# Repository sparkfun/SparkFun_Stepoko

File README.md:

SparkFun GRBL Board
========================================

[*SparkFun Stepoko (ROB-13155)*](https://www.sparkfun.com/products/13155)

A 3 axis motor controller for use with grbl.

Repository Contents (template)
-------------------

* **/Examples** - Example gcode files, projects, and settings
* **/Hardware** - Eagle design files (.brd, .sch)
* **/Mechanical** - Enclosure and heatsink mechanical drawings
* **/Production** - Production panel files (.brd)

Documentation
--------------
* **Hookup Guide** - Basic hookup guide for the Stepoko
* **Coaster Project Tutorial** - Process of creating the coaster example
* **[SparkFun Fritzing repo](https://github.com/sparkfun/Fritzing_Parts)** - Fritzing diagrams for SparkFun products.
* **[SparkFun 3D Model repo](https://github.com/sparkfun/3D_Models)** - 3D models of SparkFun products. 

Product Versions
----------------
[*SparkFun Stepoko (ROB-13155)*](https://www.sparkfun.com/products/13155)

Version History
---------------
* [v1.0](https://github.com/sparkfun/SparkFun_Stepoko/tree/V_1_0) - Released to Reds
* [v1.1](https://github.com/sparkfun/SparkFun_Stepoko/tree/V_1_1) - Changed pot symbol name and 'top-side' resistor value
* [v1.2](https://github.com/sparkfun/SparkFun_Stepoko/tree/V_1_2) - Updated capacitor values, documentation finished

License Information
-------------------

This product is _**open source**_! 

Please review the LICENSE.md file for license information. 

If you have any questions or concerns on licensing, please contact techsupport@sparkfun.com.

Distributed as-is; no warranty is given.

- Your friends at SparkFun.

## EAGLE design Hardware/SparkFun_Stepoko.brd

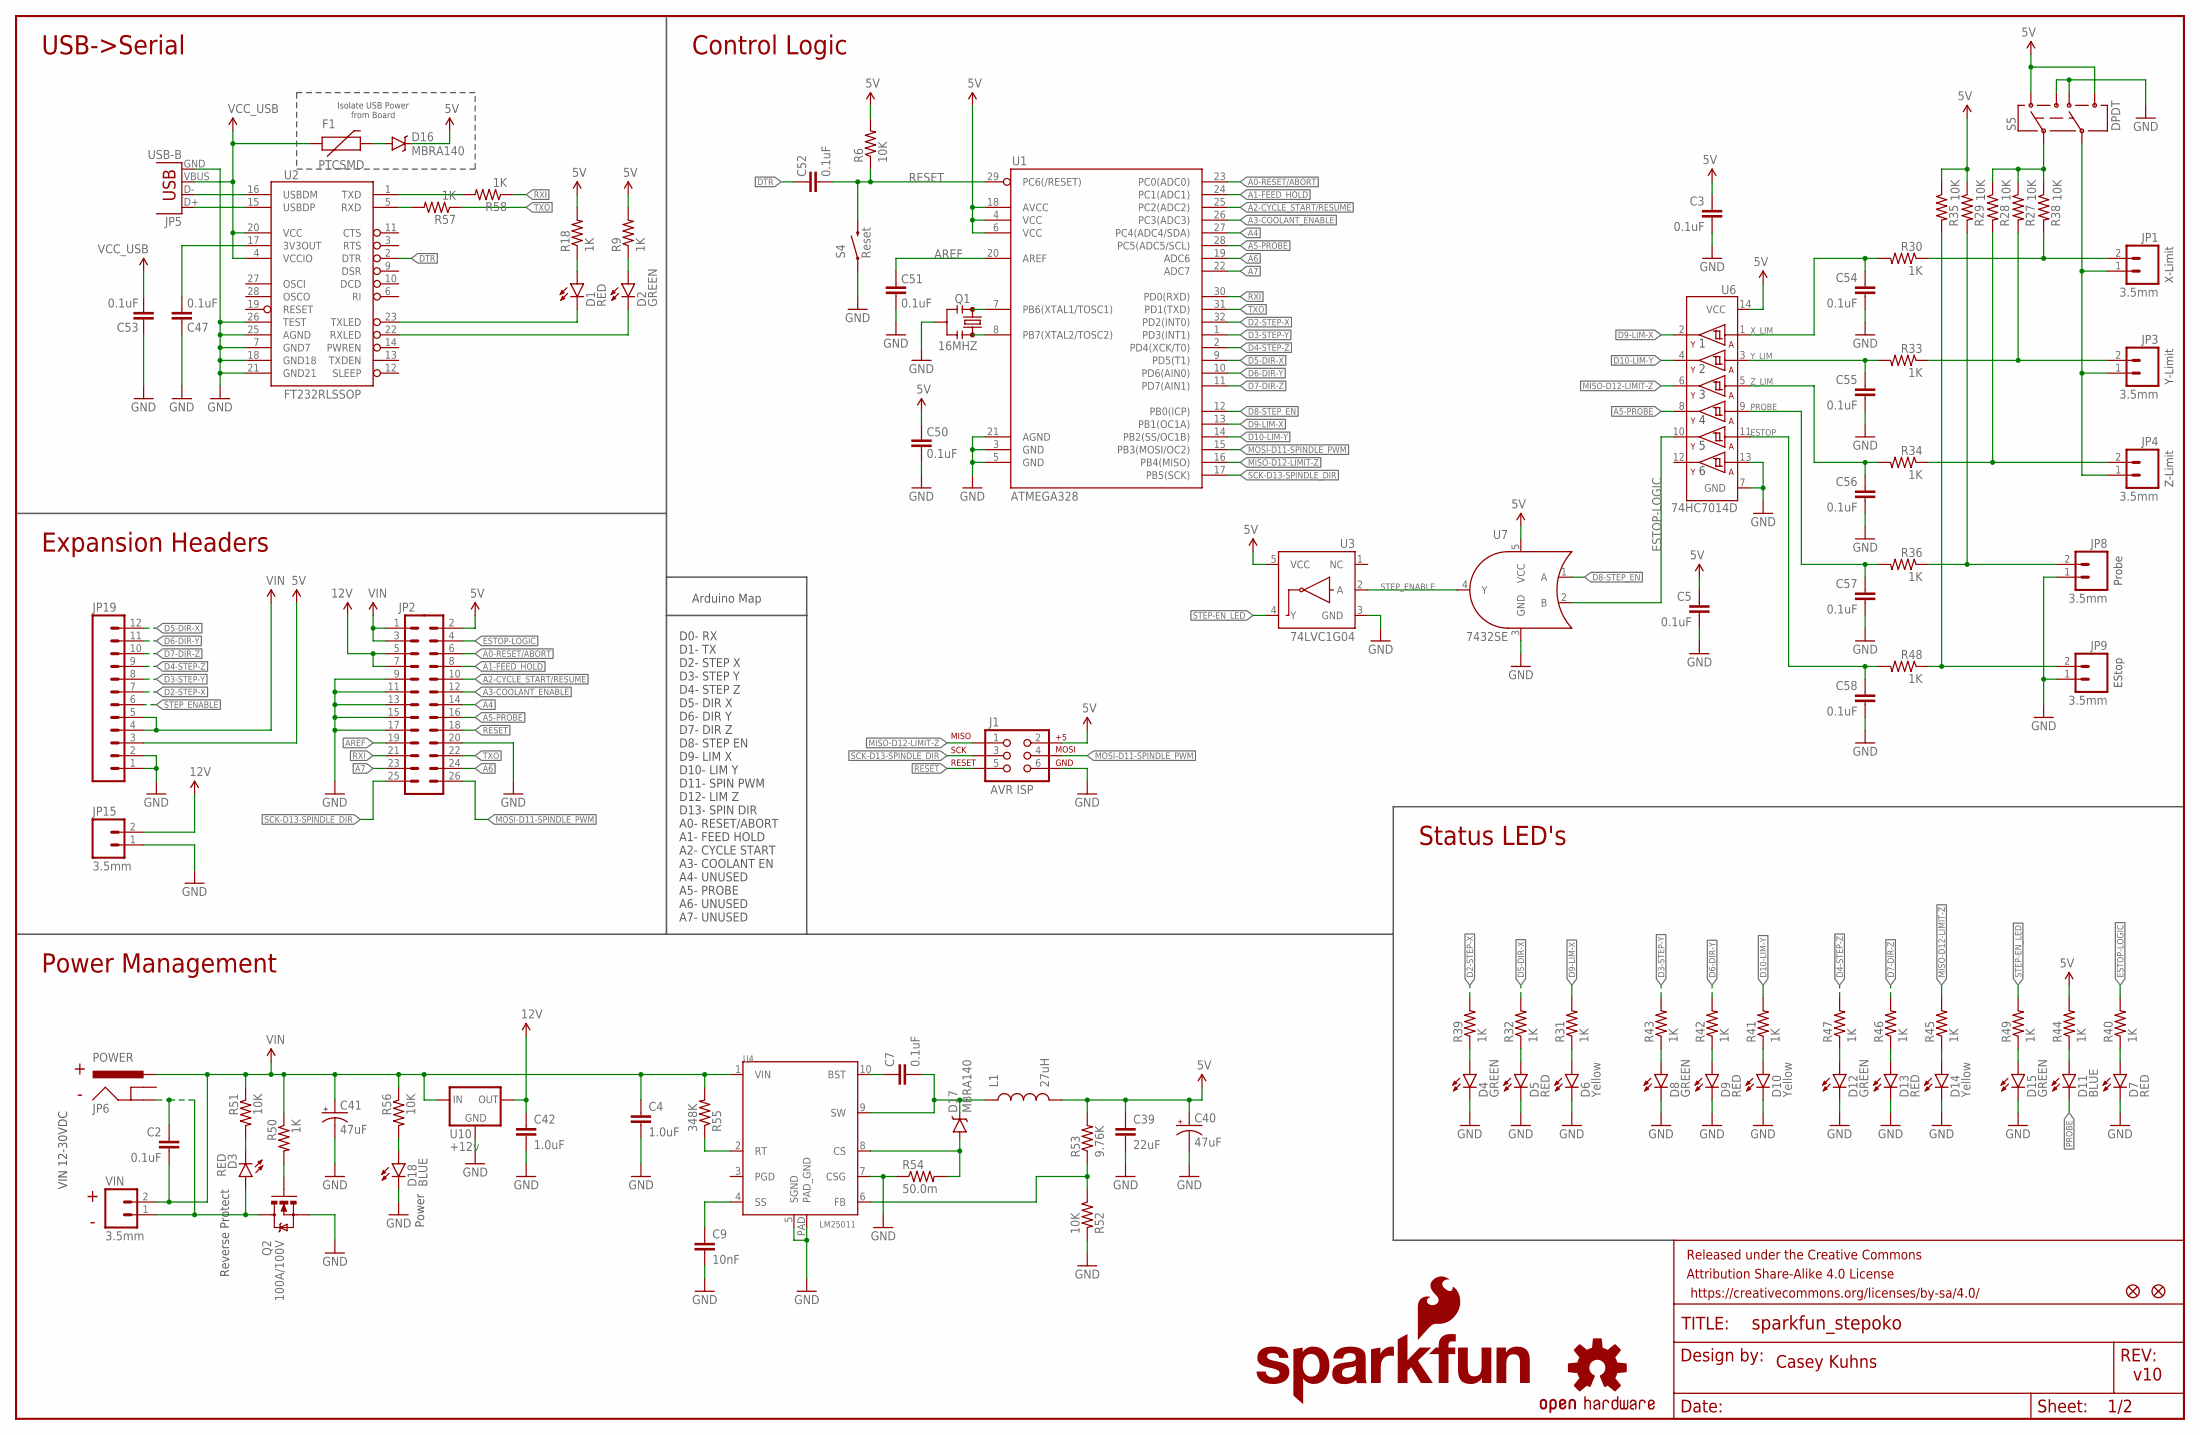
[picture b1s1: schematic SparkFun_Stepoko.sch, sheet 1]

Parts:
C2, C3, C5, C7, C47, C50, C51, C52, C53, C54, C55, C56, C57, C58: 0.1uF; 0603-CAP
C4, C42: 1.0uF; 1206-CAP
C9: 10nF; 0603-CAP
C39: 22uF; 1210
C40, C41: 47uF; PANASONIC_D
D1, D3, D5, D7, D9, D13: RED; LED-1206
D2, D4, D8, D12, D15: GREEN; LED-1206
D6, D10, D14: Yellow; LED-1206
D11, D18: BLUE; LED-1206
D16, D17: MBRA140; SMA-DIODE
F1: PTCSMD; PTC-1206
FID1, FID2: FIDUCIAL1X2; FIDUCIAL-1X2
FRAME1: FRAME-LEDGER; CREATIVE_COMMONS
J1: AVR ISP; 2X3
JP1, JP3, JP4, JP8, JP9, JP15: 3.5mm; SCREWTERMINAL-3.5MM-2_LOCK
JP2: M13X22X13; 2X13
JP5: USB-B; USB-B-PTH
JP6: POWER; POWER_JACK_PTH_LOCK
JP19: M12PTH; 1X12
L1: 27uH; INDUCTOR_SDR1307
LOGO1: OSHW-LOGOM; OSHW-LOGO-M
LOGO3: SFE_LOGO_NAME_FLAME.2_INCH; SFE_LOGO_NAME_FLAME_.2
Q1: 16MHZ; RESONATOR-SMD
Q2: 100A/100V; TO-263/D2PAK
R6, R27, R28, R29, R35, R38, R51, R52, R56: 10K; 0603-RES
R9, R18, R30, R33, R34, R36, R48, R50, R57, R58: 1K; 0603-RES@1
R31, R32, R39, R40, R41, R42, R43, R44, R45, R46, R47, R49: 1K; 0603-RES
R53: 9.76K; 0603
R54: 50.0m; 0603
R55: 348K; 0603
S4: Reset; TACTILE-SWITCH-SMD
S5: DPDT; AYZ0202
U1: ATMEGA328; TQFP32-08@1
U2: FT232RLSSOP; SSOP28DB
U3: 74LVC1G04; SOT353
U4: LM25011; HVSS0P-10
U6: 74HC7014D; SOIC-14
U7: 7432SE; SOT353
U10: +12v; TO-252
VIN: 3.5mm; SCREWTERMINAL-3.5MM-2_LOCK

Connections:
5V: C3.1, C5.1, C39.1, C40.+, C50.2, D16.C, J1.2, JP2.2, JP19.3, L1.P$2 (2), R6.2, R9.2, R18.2, R29.1, R35.1, R44.2, R53.2, S5.1, S5.6, U1.4 (VCC), U1.6 (VCC), U1.18 (AVCC), U3.5 (VCC), U6.14 (VCC), U7.5 (VCC); also elsewhere on the board
A0-RESET/ABORT: JP2.6, U1.23 (PC0(ADC0))
A1-FEED_HOLD: JP2.8, U1.24 (PC1(ADC1))
A2-CYCLE_START/RESUME: JP2.10, U1.25 (PC2(ADC2))
A3-COOLANT_ENABLE: JP2.12, U1.26 (PC3(ADC3))
A4: JP2.14, U1.27 (PC4(ADC4/SDA))
A5-PROBE: JP2.16, U1.28 (PC5(ADC5/SCL)), U6.8 (4Y)
A6: JP2.24, U1.19 (ADC6)
A7: JP2.23, U1.22 (ADC7)
AREF: C51.2, JP2.19, U1.20 (AREF)
D2-STEP-X: JP19.7, R39.2, U1.32 (PD2(INT0)); also elsewhere on the board
D3-STEP-Y: JP19.8, R43.2, U1.1 (PD3(INT1)); also elsewhere on the board
D4-STEP-Z: JP19.9, R47.2, U1.2 (PD4(XCK/T0)); also elsewhere on the board
D5-DIR-X: JP19.12, R32.2, U1.9 (PD5(T1)); also elsewhere on the board
D6-DIR-Y: JP19.11, R42.2, U1.10 (PD6(AIN0)); also elsewhere on the board
D7-DIR-Z: JP19.10, R46.2, U1.11 (PD7(AIN1)); also elsewhere on the board
D8-STEP_EN: U1.12 (PB0(ICP)), U7.1 (A)
D9-LIM-X: R31.2, U1.13 (PB1(OC1A)), U6.2 (1Y)
D10-LIM-Y: R41.2, U1.14 (PB2(SS/OC1B)), U6.4 (2Y)
D+: JP5.D+, U2.15 (USBDP)
D-: JP5.D-, U2.16 (USBDM)
DTR: C52.2, U2.2 (DTR)
ESTOP: C58.1, R48.2, U6.11 (5A)
ESTOP-LOGIC: JP2.4, R40.2, U6.10 (5Y), U7.2 (B)
GND: C3.2, C4.2, C5.2, C9.2, C39.2, C40.-, C41.-, C42.2, C47.2, C50.1, C51.1, C53.2, C54.2, C55.2, C56.2, C57.2, C58.2, D4.C, D5.C, D6.C, D7.C, D8.C, D9.C, D10.C, D12.C, D13.C, D14.C, D15.C, D18.C, J1.6, JP2.9, JP2.11, JP2.13, JP2.15, JP2.17, JP2.20, JP5.GND, JP8.1, JP9.1, JP15.1, JP19.1, JP19.2, Q1.2, Q2.3 (S), R52.2, R54.1, S4.1, S5.3, S5.4, U1.3 (GND), U1.5 (GND), U1.21 (AGND), U2.7 (GND7), U2.18 (GND18), U2.21 (GND21), U2.25 (AGND), U2.26 (TEST), U3.3 (GND), U4.5 (SGND), U4.7 (CSG), U4.PAD (PAD_GND), U6.7 (GND), U6.13 (6A), U7.3 (GND), U10.3 (GND); also elsewhere on the board
MISO-D12-LIMIT-Z: J1.1, R45.2, U1.16 (PB4(MISO)), U6.6 (3Y)
MOSI-D11-SPINDLE_PWM: J1.4, JP2.26, U1.15 (PB3(MOSI/OC2))
unnamed: R58.2, U2.1 (TXD)
unnamed: D2.A, R9.1
unnamed: D1.A, R18.1
unnamed: JP1.1, JP3.1, JP4.1, S5.5
unnamed: D7.A, R40.1
unnamed: Q1.3, U1.8 (PB7(XTAL2/TOSC2))
unnamed: JP1.2, R30.1, R38.2
unnamed: Q1.1, U1.7 (PB6(XTAL1/TOSC1))
unnamed: D11.A, R44.1
unnamed: D15.A, R49.1
unnamed: C2.1, D3.A, JP6.GND, Q2.2 (D), VIN.1
unnamed: D6.A, R31.1
unnamed: D5.A, R32.1
unnamed: D4.A, R39.1
unnamed: R52.1, R53.1, U4.6 (FB)
unnamed: D10.A, R41.1
unnamed: D9.A, R42.1
unnamed: D1.C, U2.23 (TXLED)
unnamed: D2.C, U2.22 (RXLED)
unnamed: D8.A, R43.1
unnamed: Q2.1 (G), R50.2
unnamed: D14.A, R45.1
unnamed: D3.C, R51.2
unnamed: JP3.2, R27.2, R33.1
unnamed: JP4.2, R28.2, R34.1
unnamed: D16.A, F1.2
unnamed: JP8.2, R29.2, R36.1
unnamed: JP9.2, R35.2, R48.1
unnamed: D18.A, R56.2
unnamed: D13.A, R46.1
unnamed: D12.A, R47.1
unnamed: R57.2, U2.5 (RXD)
unnamed: R55.1, U4.2 (RT)
unnamed: C7.1, U4.10 (BST)
unnamed: C7.2, D17.C, L1.P$1 (1), U4.9 (SW)
unnamed: C9.1, U4.4 (SS)
unnamed: R27.1, R28.1, R38.1, S5.2
unnamed: D17.A, R54.2, U4.8 (CS)
unnamed: C47.1, U2.17 (3V3OUT)
PROBE: C57.1, D11.C, R36.2, U6.9 (4A)
RESET: C52.1, J1.5, JP2.18, R6.1, S4.3 (2), U1.29 (PC6(/RESET))
RXI: JP2.21, R58.1, U1.30 (PD0(RXD))
SCK-D13-SPINDLE_DIR: J1.3, JP2.25, U1.17 (PB5(SCK))
STEP-EN_LED: R49.2, U3.4 (Y)
STEP_ENABLE: JP19.6, U3.2 (A), U7.4 (Y); also elsewhere on the board
TXO: JP2.22, R57.1, U1.31 (PD1(TXD))
VCC: C42.1, JP2.5, JP2.7, JP15.2, U10.2 (OUT)
VCC_USB: C53.1, F1.1, JP5.VBUS, U2.4 (VCCIO), U2.20 (VCC)
VIN: C2.2, C4.1, C41.+, JP2.1, JP2.3, JP6.PWR, JP19.4, JP19.5, R50.1, R51.1, R55.2, R56.1, U4.1 (VIN), U10.1 (IN), VIN.2; also elsewhere on the board
X_LIM: C54.1, R30.2, U6.1 (1A)
Y_LIM: C55.1, R33.2, U6.3 (2A)
Z_LIM: C56.1, R34.2, U6.5 (3A)

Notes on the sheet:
X-Limit
Y-Limit
Z-Limit
Probe
EStop
Isolate USB Power from Board
Status LED's
Power Management
Expansion Headers
USB->Serial
Control Logic
Reverse Protect
Power
Casey Kuhns
v10
D0- RX D1- TX D2- STEP X D3- STEP Y D4- STEP Z D5- DIR X D6- DIR Y D7- DIR Z D8- STEP EN D9- LIM X D10- LIM Y D11- SPIN PWM D12- LIM Z D13- SPIN DIR A0- RESET/ABORT A1- FEED HOLD A2- CYCLE START A3- COOLANT EN A4- UNUSED A5- PROBE A6- UNUSED A7- UNUSED
Arduino Map
VIN 12-30VDC

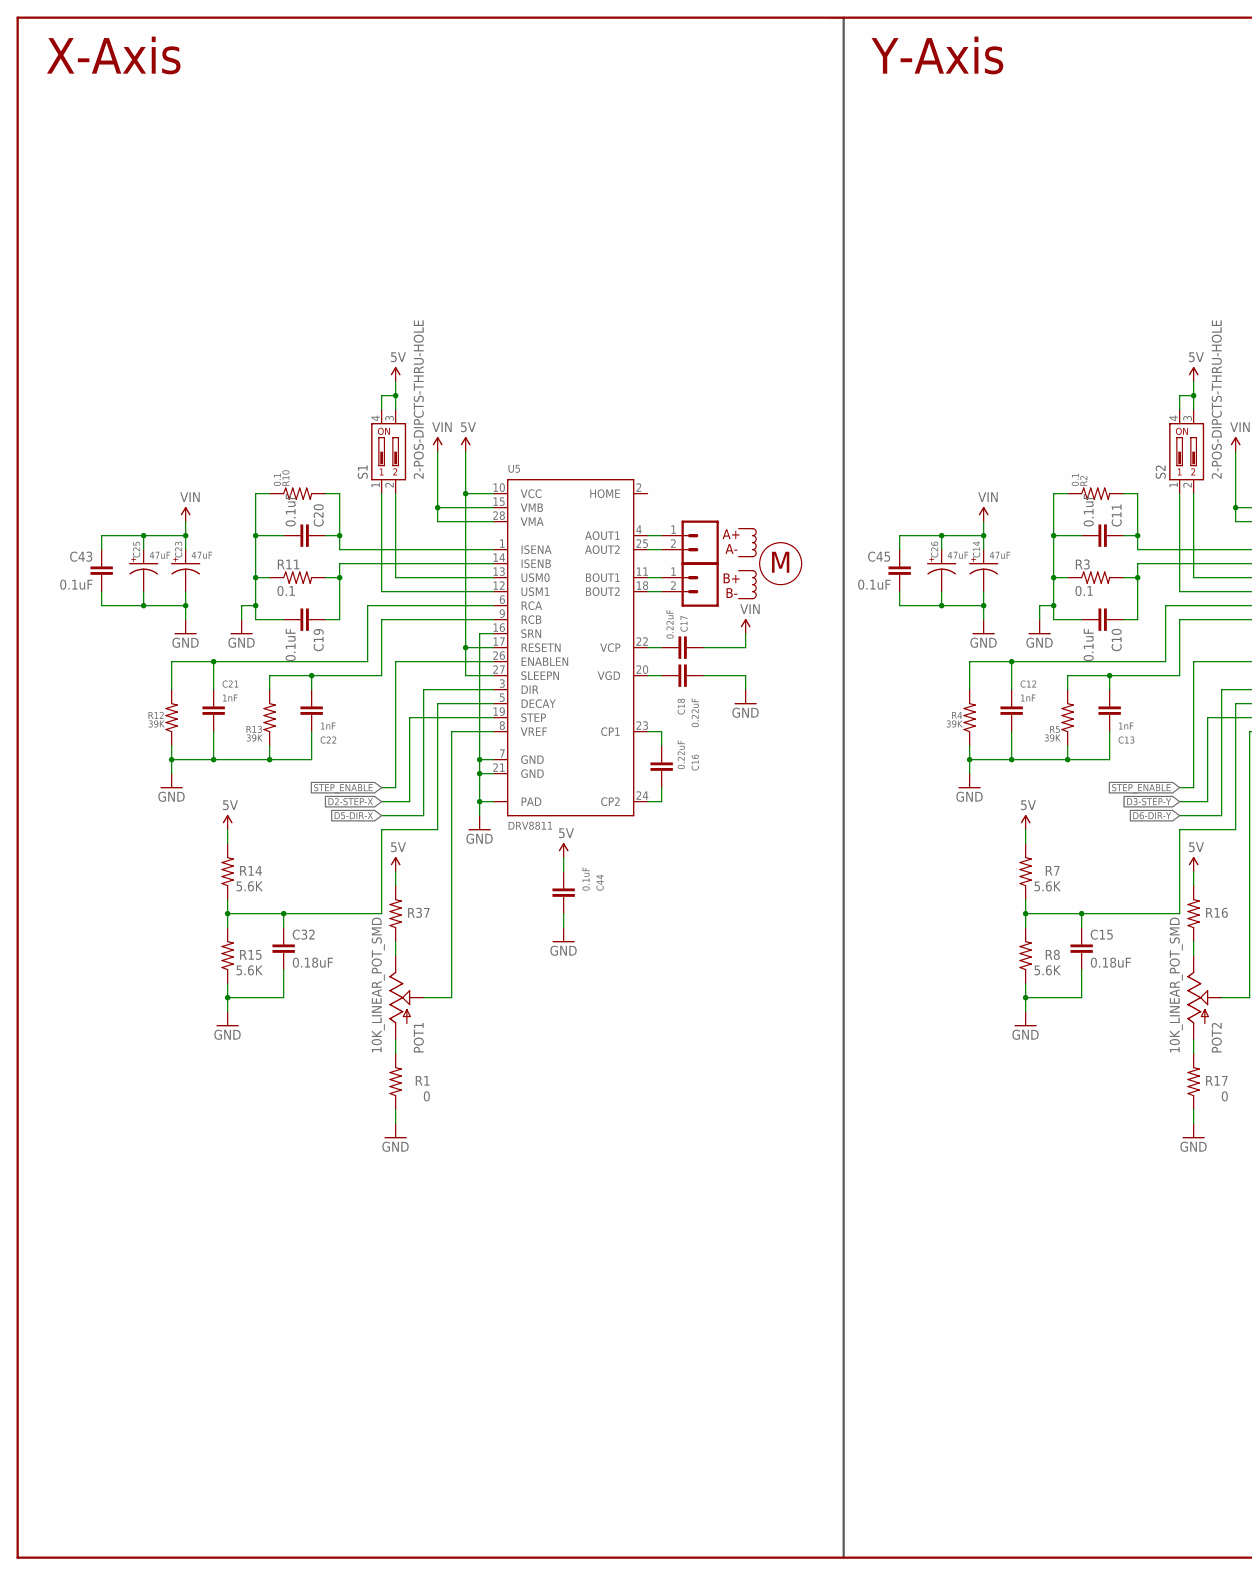
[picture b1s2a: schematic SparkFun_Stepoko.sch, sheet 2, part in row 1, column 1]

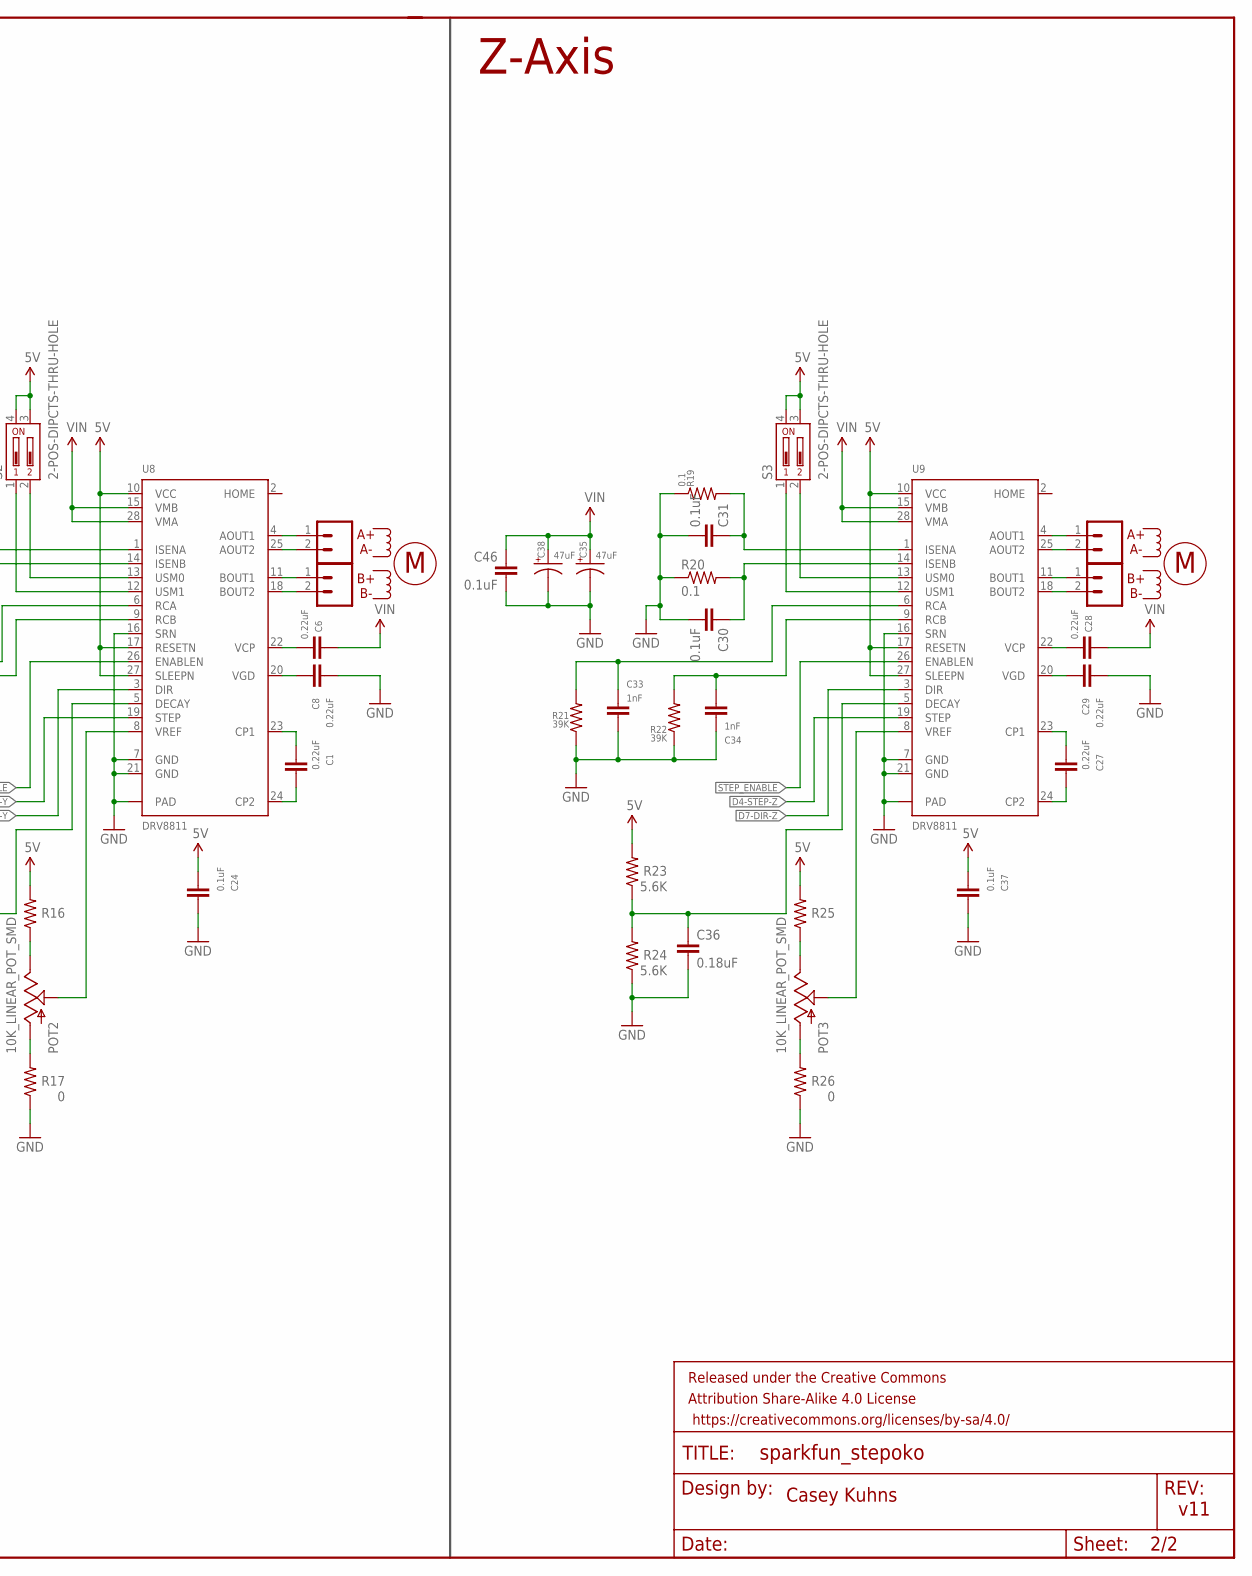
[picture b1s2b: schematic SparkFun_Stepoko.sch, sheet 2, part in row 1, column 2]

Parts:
C1, C6, C8, C16, C17, C18, C27, C28, C29: 0.22uF; 0603-CAP
C10, C11, C19, C20, C24, C30, C31, C37, C43, C44, C45, C46: 0.1uF; 0603-CAP
C12, C13, C21, C22, C33, C34: 1nF; 0603-CAP
C14, C23, C25, C26, C35, C38: 47uF; PANASONIC_D
C15, C32, C36: 0.18uF; 0603
FRAME2: FRAME-LEDGER; CREATIVE_COMMONS
POT1, POT2, POT3: 10K_LINEAR_POT_SMD; TC33X
R1, R17, R26: 0; 0603
R2, R3, R10, R11, R19, R20: 0.1; 1210
R4, R5, R12, R13, R21, R22: 39K; 0603
R7, R8, R14, R15, R23, R24: 5.6K; 0603
R16, R25, R37: 10K; 0603-RES
S1, S2, S3: 2-POS-DIPCTS-THRU-HOLE; 209-2LPST
U5, U8, U9: DRV8811; HTSSOP28
X-A: 3.5mm; SCREWTERMINAL-3.5MM-2_LOCK
X-B: 3.5mm; SCREWTERMINAL-3.5MM-2_LOCK
Y-A: 3.5mm; SCREWTERMINAL-3.5MM-2_LOCK
Y-B: 3.5mm; SCREWTERMINAL-3.5MM-2_LOCK
Z-A: 3.5mm; SCREWTERMINAL-3.5MM-2_LOCK
Z-B: 3.5mm; SCREWTERMINAL-3.5MM-2_LOCK

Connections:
5V: C24.1, C37.1, C44.1, R7.2, R14.2, R16.2, R23.2, R25.2, R37.2, S1.3, S1.4, S2.3, S2.4, S3.3, S3.4, U5.10 (VCC), U5.17 (RESETN), U5.27 (SLEEPN), U8.10 (VCC), U8.17 (RESETN), U8.27 (SLEEPN), U9.10 (VCC), U9.17 (RESETN), U9.27 (SLEEPN); also elsewhere on the board
D2-STEP-X: U5.19 (STEP); also elsewhere on the board
D3-STEP-Y: U8.19 (STEP); also elsewhere on the board
D4-STEP-Z: U9.19 (STEP); also elsewhere on the board
D5-DIR-X: U5.3 (DIR); also elsewhere on the board
D6-DIR-Y: U8.3 (DIR); also elsewhere on the board
D7-DIR-Z: U9.3 (DIR); also elsewhere on the board
GND: C8.1, C10.2, C11.2, C12.2, C13.2, C14.-, C15.2, C18.1, C19.2, C20.2, C21.2, C22.2, C23.-, C24.2, C25.-, C26.-, C29.1, C30.2, C31.2, C32.2, C33.2, C34.2, C35.-, C36.2, C37.2, C38.-, C43.2, C44.2, C45.2, C46.2, R1.1, R2.1, R3.1, R4.1, R5.1, R8.1, R10.1, R11.1, R12.1, R13.1, R15.1, R17.1, R19.1, R20.1, R21.1, R22.1, R24.1, R26.1, U5.7 (GND), U5.16 (SRN), U5.21 (GND), U5.GND@10 (PAD), U5.GND@11 (PAD), U5.GND@12 (PAD), U5.GND@13 (PAD), U5.GND@14 (PAD), U5.GND@15 (PAD), U5.GND@16 (PAD), U5.GND@17 (PAD), U5.GND@18 (PAD), U5.GND@19 (PAD), U5.GND@20 (PAD), U5.GND@21 (PAD), U5.GND@22 (PAD), U5.GND@23 (PAD), U5.GND@24 (PAD), U5.GND@25 (PAD), U5.GND@26 (PAD), U5.GND@27 (PAD), U5.GND@28 (PAD), U5.GND@29 (PAD), U5.GND@30 (PAD), U5.GND@PAD (PAD), U8.7 (GND), U8.16 (SRN), U8.21 (GND), U8.GND@10 (PAD), U8.GND@11 (PAD), U8.GND@12 (PAD), U8.GND@13 (PAD), U8.GND@14 (PAD), U8.GND@15 (PAD), U8.GND@16 (PAD), U8.GND@17 (PAD), U8.GND@18 (PAD), U8.GND@19 (PAD), U8.GND@20 (PAD), U8.GND@21 (PAD), U8.GND@22 (PAD), U8.GND@23 (PAD), U8.GND@24 (PAD), U8.GND@25 (PAD), U8.GND@26 (PAD), U8.GND@27 (PAD), U8.GND@28 (PAD), U8.GND@29 (PAD), U8.GND@30 (PAD), U8.GND@PAD (PAD), U9.7 (GND), U9.16 (SRN), U9.21 (GND), U9.GND@10 (PAD), U9.GND@11 (PAD), U9.GND@12 (PAD), U9.GND@13 (PAD), U9.GND@14 (PAD), U9.GND@15 (PAD), U9.GND@16 (PAD), U9.GND@17 (PAD), U9.GND@18 (PAD), U9.GND@19 (PAD), U9.GND@20 (PAD), U9.GND@21 (PAD), U9.GND@22 (PAD), U9.GND@23 (PAD), U9.GND@24 (PAD), U9.GND@25 (PAD), U9.GND@26 (PAD), U9.GND@27 (PAD), U9.GND@28 (PAD), U9.GND@29 (PAD), U9.GND@30 (PAD), U9.GND@PAD (PAD); also elsewhere on the board
unnamed: POT1.3 (E), R37.1
unnamed: POT1.1 (A), R1.2
unnamed: C12.1, R4.2, U8.6 (RCA)
unnamed: C13.1, R5.2, U8.9 (RCB)
unnamed: C15.1, R7.1, R8.2, U8.5 (DECAY)
unnamed: S2.2, U8.13 (USM0)
unnamed: S2.1, U8.12 (USM1)
unnamed: C16.1, U5.24 (CP2)
unnamed: C16.2, U5.23 (CP1)
unnamed: C8.2, U8.20 (VGD)
unnamed: POT2.2 (S), U8.8 (VREF)
unnamed: C21.1, R12.2, U5.6 (RCA)
unnamed: C22.1, R13.2, U5.9 (RCB)
unnamed: C32.1, R14.1, R15.2, U5.5 (DECAY)
unnamed: S1.2, U5.13 (USM0)
unnamed: S1.1, U5.12 (USM1)
unnamed: U5.11 (BOUT1), X-B.1
unnamed: C18.2, U5.20 (VGD)
unnamed: POT2.3 (E), R16.1
unnamed: POT2.1 (A), R17.2
unnamed: C6.2, U8.22 (VCP)
unnamed: C1.1, U8.24 (CP2)
unnamed: C1.2, U8.23 (CP1)
unnamed: U8.11 (BOUT1), Y-B.1
unnamed: U8.18 (BOUT2), Y-B.2
unnamed: U8.4 (AOUT1), Y-A.1
unnamed: U8.25 (AOUT2), Y-A.2
unnamed: C10.1, R3.2, U8.14 (ISENB)
unnamed: C17.2, U5.22 (VCP)
unnamed: U5.18 (BOUT2), X-B.2
unnamed: U5.4 (AOUT1), X-A.1
unnamed: C11.1, R2.2, U8.1 (ISENA)
unnamed: C33.1, R21.2, U9.6 (RCA)
unnamed: C34.1, R22.2, U9.9 (RCB)
unnamed: C36.1, R23.1, R24.2, U9.5 (DECAY)
unnamed: S3.2, U9.13 (USM0)
unnamed: S3.1, U9.12 (USM1)
unnamed: U5.25 (AOUT2), X-A.2
unnamed: C29.2, U9.20 (VGD)
unnamed: POT3.2 (S), U9.8 (VREF)
unnamed: POT3.3 (E), R25.1
unnamed: POT3.1 (A), R26.2
unnamed: C28.2, U9.22 (VCP)
unnamed: C27.1, U9.24 (CP2)
unnamed: C27.2, U9.23 (CP1)
unnamed: U9.11 (BOUT1), Z-B.1
unnamed: U9.18 (BOUT2), Z-B.2
unnamed: U9.4 (AOUT1), Z-A.1
unnamed: U9.25 (AOUT2), Z-A.2
unnamed: C30.1, R20.2, U9.14 (ISENB)
unnamed: C19.1, R11.2, U5.14 (ISENB)
unnamed: C31.1, R19.2, U9.1 (ISENA)
unnamed: POT1.2 (S), U5.8 (VREF)
unnamed: C20.1, R10.2, U5.1 (ISENA)
STEP_ENABLE: U5.26 (ENABLEN), U8.26 (ENABLEN), U9.26 (ENABLEN); also elsewhere on the board
VIN: C6.1, C14.+, C17.1, C23.+, C25.+, C26.+, C28.1, C35.+, C38.+, C43.1, C45.1, C46.1, U5.15 (VMB), U5.28 (VMA), U8.15 (VMB), U8.28 (VMA), U9.15 (VMB), U9.28 (VMA); also elsewhere on the board

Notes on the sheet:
X-Axis
Y-Axis
Z-Axis
v11
Casey Kuhns
A+ A- B+ B-

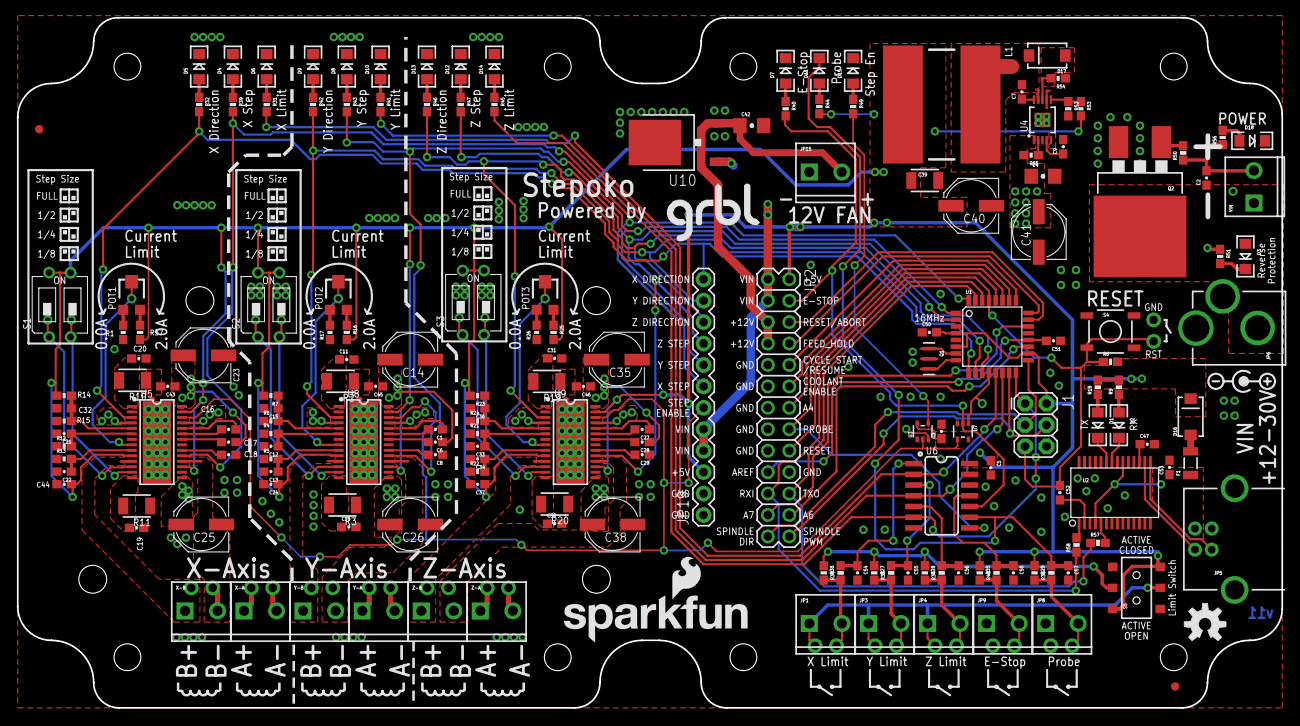
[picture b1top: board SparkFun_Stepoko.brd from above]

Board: 2 copper layers, 149.9 x 81.8 mm, 184 parts (1 on the bottom side), 133 nets.

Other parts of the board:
LOGO2: SFE_LOGO_NAME_FLAME.2_INCH; SFE_LOGO_NAME_FLAME_.2@1
U$1: FLANGED_RED_ENCLOSURE-DIMENSION-NO-INNER-HOLES
U$2, U$3, U$4, U$5: STAND-OFF

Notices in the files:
parts and their libraries:
SparkFun-Aesthetics: Licensing: CC v3.0 Share-Alike You are welcome to use this library for commercial purposes.
SparkFun-Aesthetics: Released under the Creative Commons Attribution Share-Alike 4.0 License
SparkFun-Aesthetics: https://creativecommons.org/licenses/by-sa/4.0
